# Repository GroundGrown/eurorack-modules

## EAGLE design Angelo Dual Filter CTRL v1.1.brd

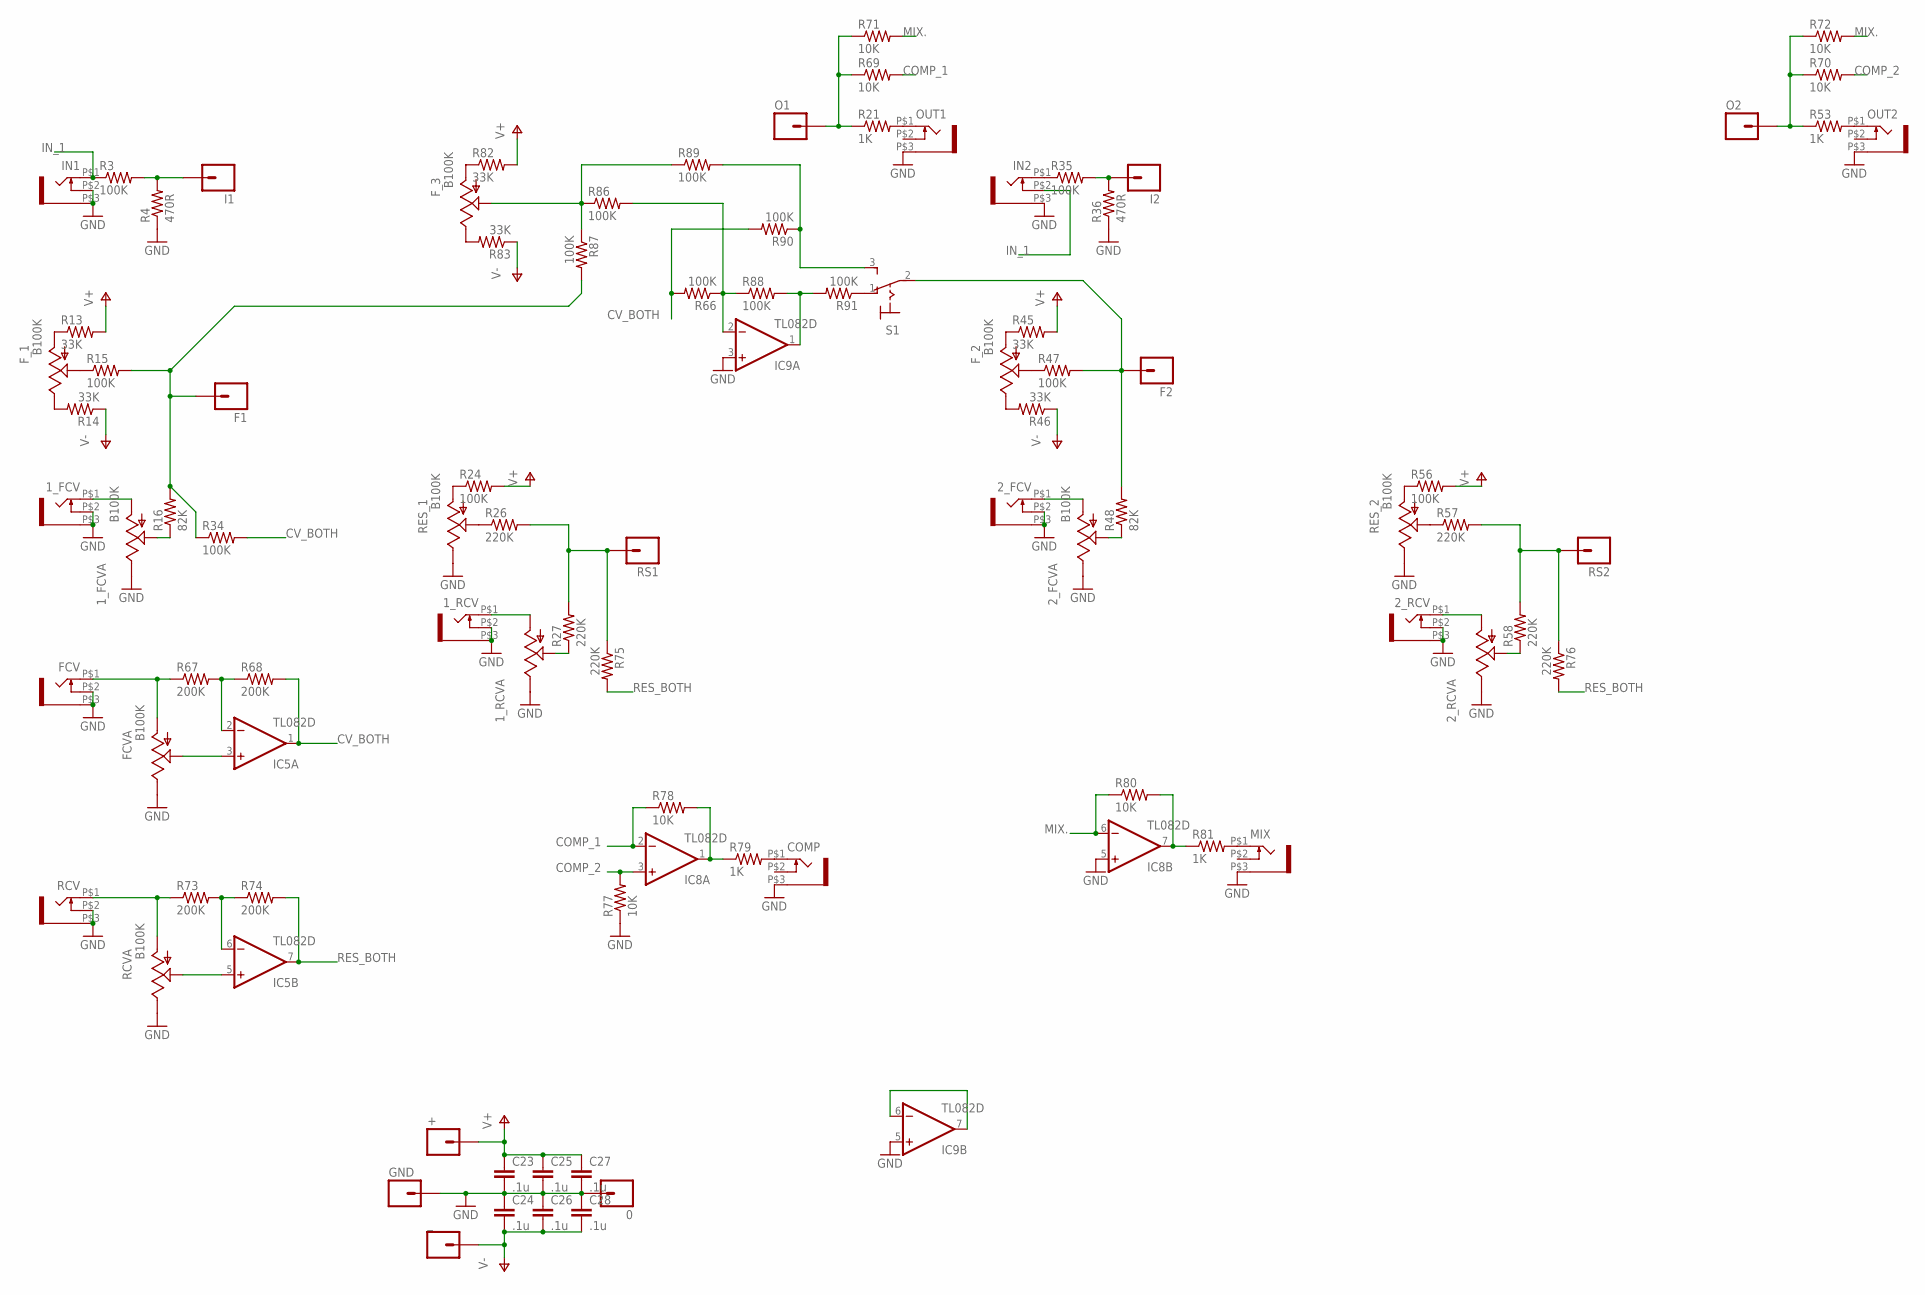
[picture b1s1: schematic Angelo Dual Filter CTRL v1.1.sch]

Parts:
0: M01PTH; 1X01
1_FCV, 1_RCV, 2_FCV, 2_RCV: WQP-PJ301M-12_JACK
1_FCVA, 2_FCVA: B100K; ALPS_POT
1_RCVA, 2_RCVA: POT; ALPS_POT
+: M01PTH; 1X01
C23, C24, C25, C26, C27, C28: .1u; 0805
COMP: WQP-PJ301M-12_JACK
F1, F2: M01PTH; 1X01
FCV: WQP-PJ301M-12_JACK
FCVA: B100K; ALPS_POT
F_1, F_2, F_3: B100K; ALPS_POT
GND: M01PTH; 1X01
I1, I2: M01PTH; 1X01
IC5, IC8, IC9: TL082D; SO08
IN1, IN2: WQP-PJ301M-12_JACK
MIX: WQP-PJ301M-12_JACK
O1, O2: M01PTH; 1X01
OUT1, OUT2: WQP-PJ301M-12_JACK
R3, R15, R24, R34, R35, R47, R56, R66, R86, R87, R88, R89, R90, R91: 100K; 0805
R4, R36: 470R; 0805
R13, R14, R45, R46, R82, R83: 33K; 0805
R16, R48: 82K; 0805
R21, R53, R79, R81: 1K; 0805
R26, R27, R57, R58, R75, R76: 220K; 0805
R67, R68, R73, R74: 200K; 0805
R69, R70, R71, R72, R77, R78, R80: 10K; 0805
RCV: WQP-PJ301M-12_JACK
RCVA: B100K; ALPS_POT
RES_1, RES_2: B100K; ALPS_POT
RS1, RS2: M01PTH; 1X01
S1: M9040P
_: M01PTH; 1X01

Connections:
COMP_1: IC8.2 (-IN), R69.2, R78.1
COMP_2: IC8.3 (+IN), R70.2, R77.2
CV_BOTH: IC5.1 (OUT), R34.2, R66.2, R68.2, R90.2
GND: 0.1, 1_FCV.P$2 (3), 1_FCV.P$3 (1), 1_FCVA.P$1 (E), 1_RCV.P$2 (3), 1_RCV.P$3 (1), 1_RCVA.P$1 (E), 2_FCV.P$2 (3), 2_FCV.P$3 (1), 2_FCVA.P$1 (E), 2_RCV.P$2 (3), 2_RCV.P$3 (1), 2_RCVA.P$1 (E), C23.2, C24.1, C25.2, C26.1, C27.2, C28.1, COMP.P$3 (1), FCV.P$2 (3), FCV.P$3 (1), FCVA.P$1 (E), GND.1, IC8.5 (+IN), IC9.3 (+IN), IC9.5 (+IN), IN1.P$2 (3), IN1.P$3 (1), IN2.P$3 (1), MIX.P$3 (1), OUT1.P$3 (1), OUT2.P$3 (1), R4.1, R36.1, R77.1, RCV.P$2 (3), RCV.P$3 (1), RCVA.P$1 (E), RES_1.P$1 (E), RES_2.P$1 (E)
IN_1: IN1.P$1 (2), IN2.P$2 (3), R3.1
MIX.: IC8.6 (-IN), R71.2, R72.2, R80.1
unnamed: F_3.P$3 (A), R82.1
unnamed: F_3.P$1 (E), R83.2
unnamed: I1.1, R3.2, R4.2
unnamed: COMP.P$1 (2), R79.2
unnamed: F_3.P$2 (S), R86.1, R87.1, R89.1
unnamed: F2.1, R47.2, R48.2, S1.2
unnamed: IC9.2 (-IN), R66.1, R86.2, R88.1
unnamed: IC9.6 (-IN), IC9.7 (OUT)
unnamed: IC9.1 (OUT), R88.2, R91.2
unnamed: R89.2, R90.1, S1.3 (S)
unnamed: R91.1, S1.1 (O)
unnamed: MIX.P$1 (2), R81.2
unnamed: F_1.P$3 (A), R13.1
unnamed: F_1.P$1 (E), R14.2
unnamed: 1_FCV.P$1 (2), 1_FCVA.P$3 (A)
unnamed: F_1.P$2 (S), R15.1
unnamed: 1_FCVA.P$2 (S), R16.1
unnamed: F1.1, R15.2, R16.2, R34.1, R87.2
unnamed: O1.1, R21.1, R69.1, R71.1
unnamed: OUT1.P$1 (2), R21.2
unnamed: R24.1, RES_1.P$3 (A)
unnamed: R26.2, R27.2, R75.1, RS1.1
unnamed: 1_RCV.P$1 (2), 1_RCVA.P$3 (A)
unnamed: R26.1, RES_1.P$2 (S)
unnamed: 1_RCVA.P$2 (S), R27.1
unnamed: I2.1, R35.2, R36.2
unnamed: IN2.P$1 (2), R35.1
unnamed: F_2.P$3 (A), R45.1
unnamed: F_2.P$1 (E), R46.2
unnamed: 2_FCV.P$1 (2), 2_FCVA.P$3 (A)
unnamed: F_2.P$2 (S), R47.1
unnamed: 2_FCVA.P$2 (S), R48.1
unnamed: O2.1, R53.1, R70.1, R72.1
unnamed: OUT2.P$1 (2), R53.2
unnamed: R56.1, RES_2.P$3 (A)
unnamed: 2_RCV.P$1 (2), 2_RCVA.P$3 (A)
unnamed: R57.1, RES_2.P$2 (S)
unnamed: 2_RCVA.P$2 (S), R58.1
unnamed: R57.2, R58.2, R76.1, RS2.1
unnamed: IC8.7 (OUT), R80.2, R81.1
unnamed: IC5.6 (-IN), R73.2, R74.1
unnamed: R73.1, RCV.P$1 (2), RCVA.P$3 (A)
unnamed: IC5.5 (+IN), RCVA.P$2 (S)
unnamed: IC8.1 (OUT), R78.2, R79.1
unnamed: IC5.2 (-IN), R67.2, R68.1
unnamed: FCV.P$1 (2), FCVA.P$3 (A), R67.1
unnamed: FCVA.P$2 (S), IC5.3 (+IN)
RES_BOTH: IC5.7 (OUT), R74.2, R75.2, R76.2
V+: +.1, C23.1, C25.1, C27.1, IC5.8 (V+), IC8.8 (V+), IC9.8 (V+), R13.2, R24.2, R45.2, R56.2, R82.2
V-: C24.2, C26.2, C28.2, IC5.4 (V-), IC8.4 (V-), IC9.4 (V-), R14.1, R46.1, R83.1, _.1

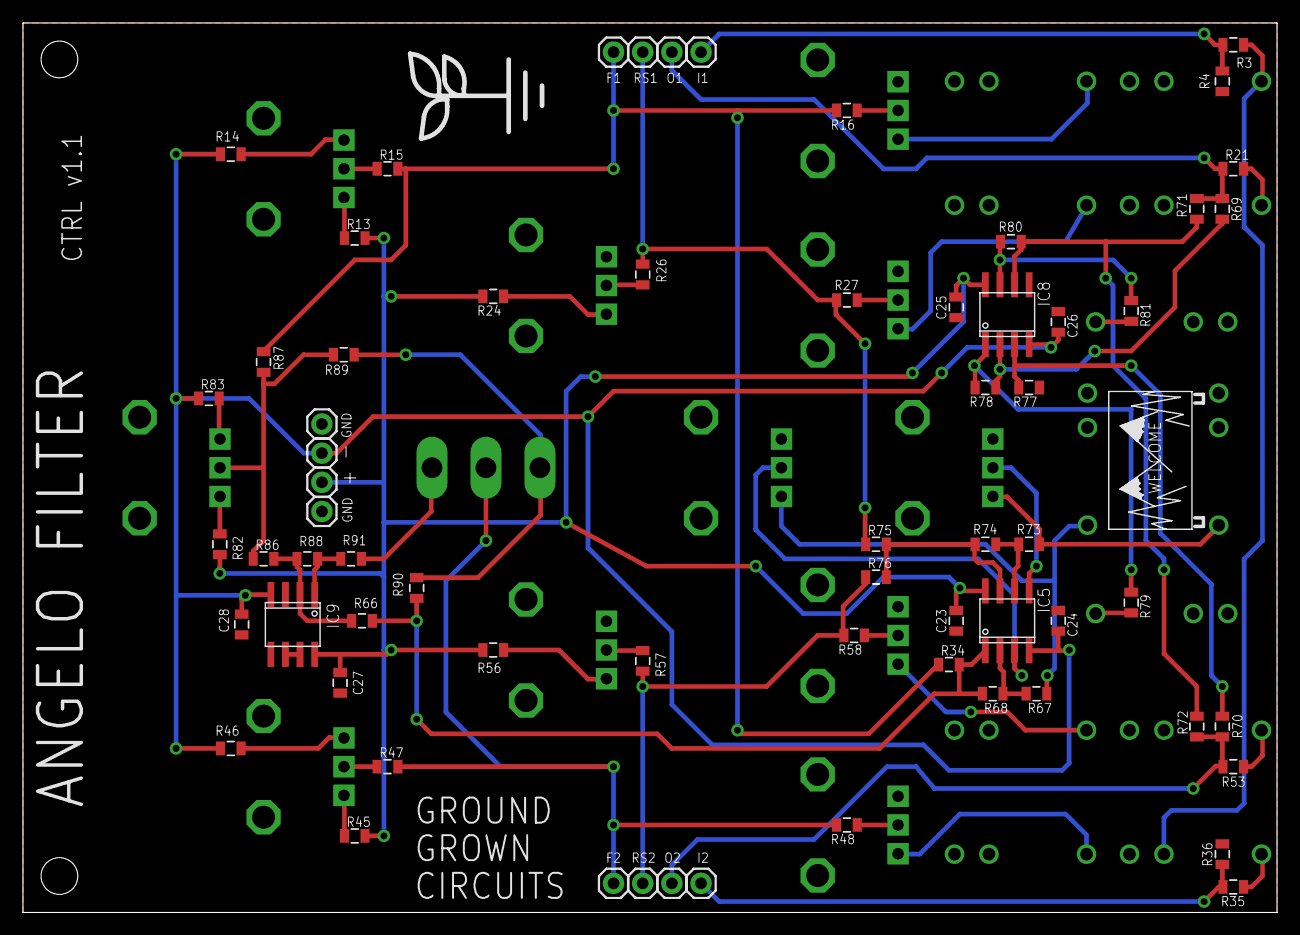
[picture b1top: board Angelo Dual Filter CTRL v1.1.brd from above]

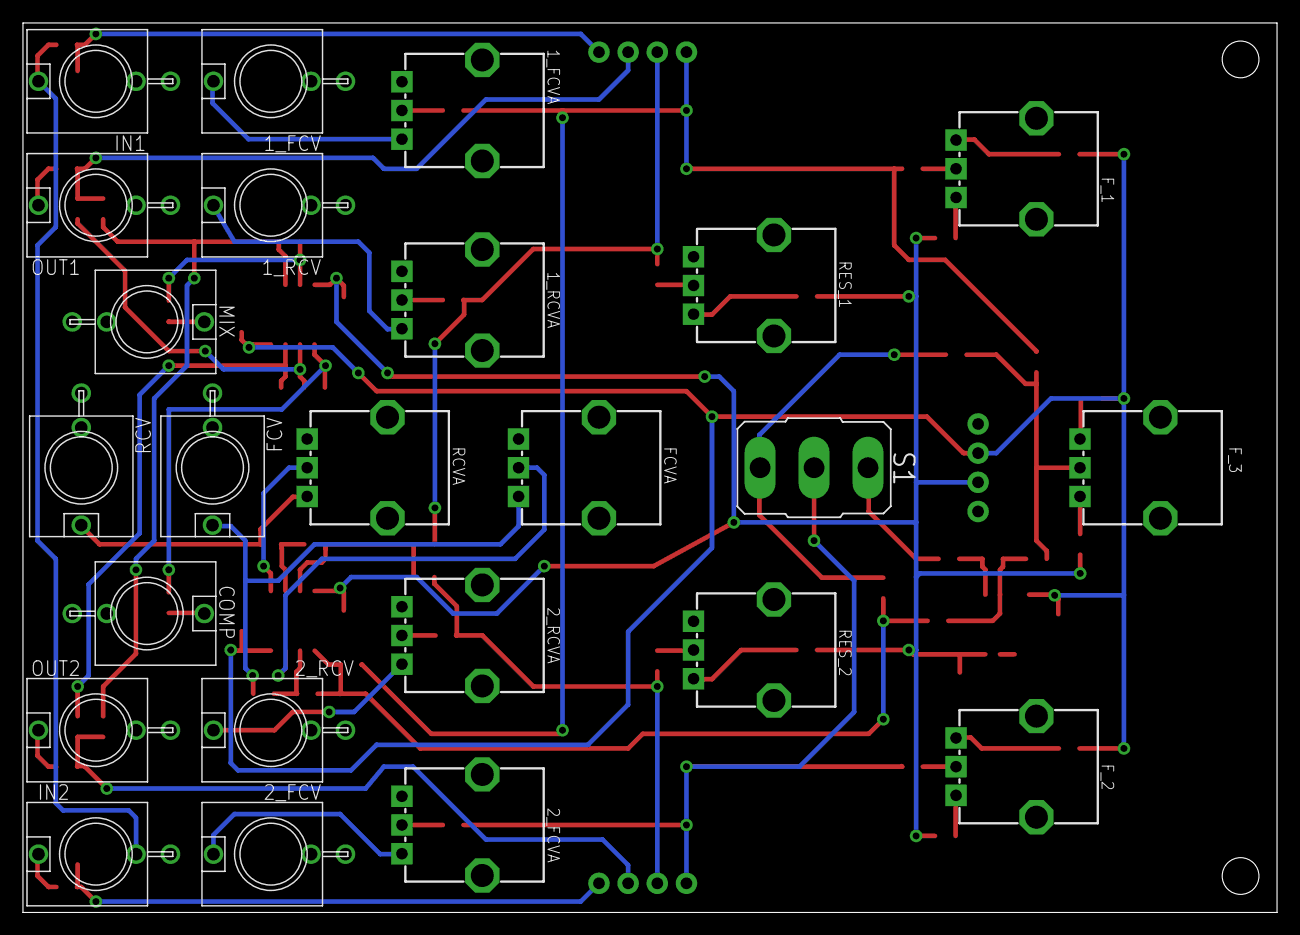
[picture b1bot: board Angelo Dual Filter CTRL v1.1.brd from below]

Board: 2 copper layers, 109.2 x 77.5 mm, 92 parts (24 on the bottom side), 56 nets.

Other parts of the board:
U$1: LOGO_MED
U$2: WELCOME_SIGN

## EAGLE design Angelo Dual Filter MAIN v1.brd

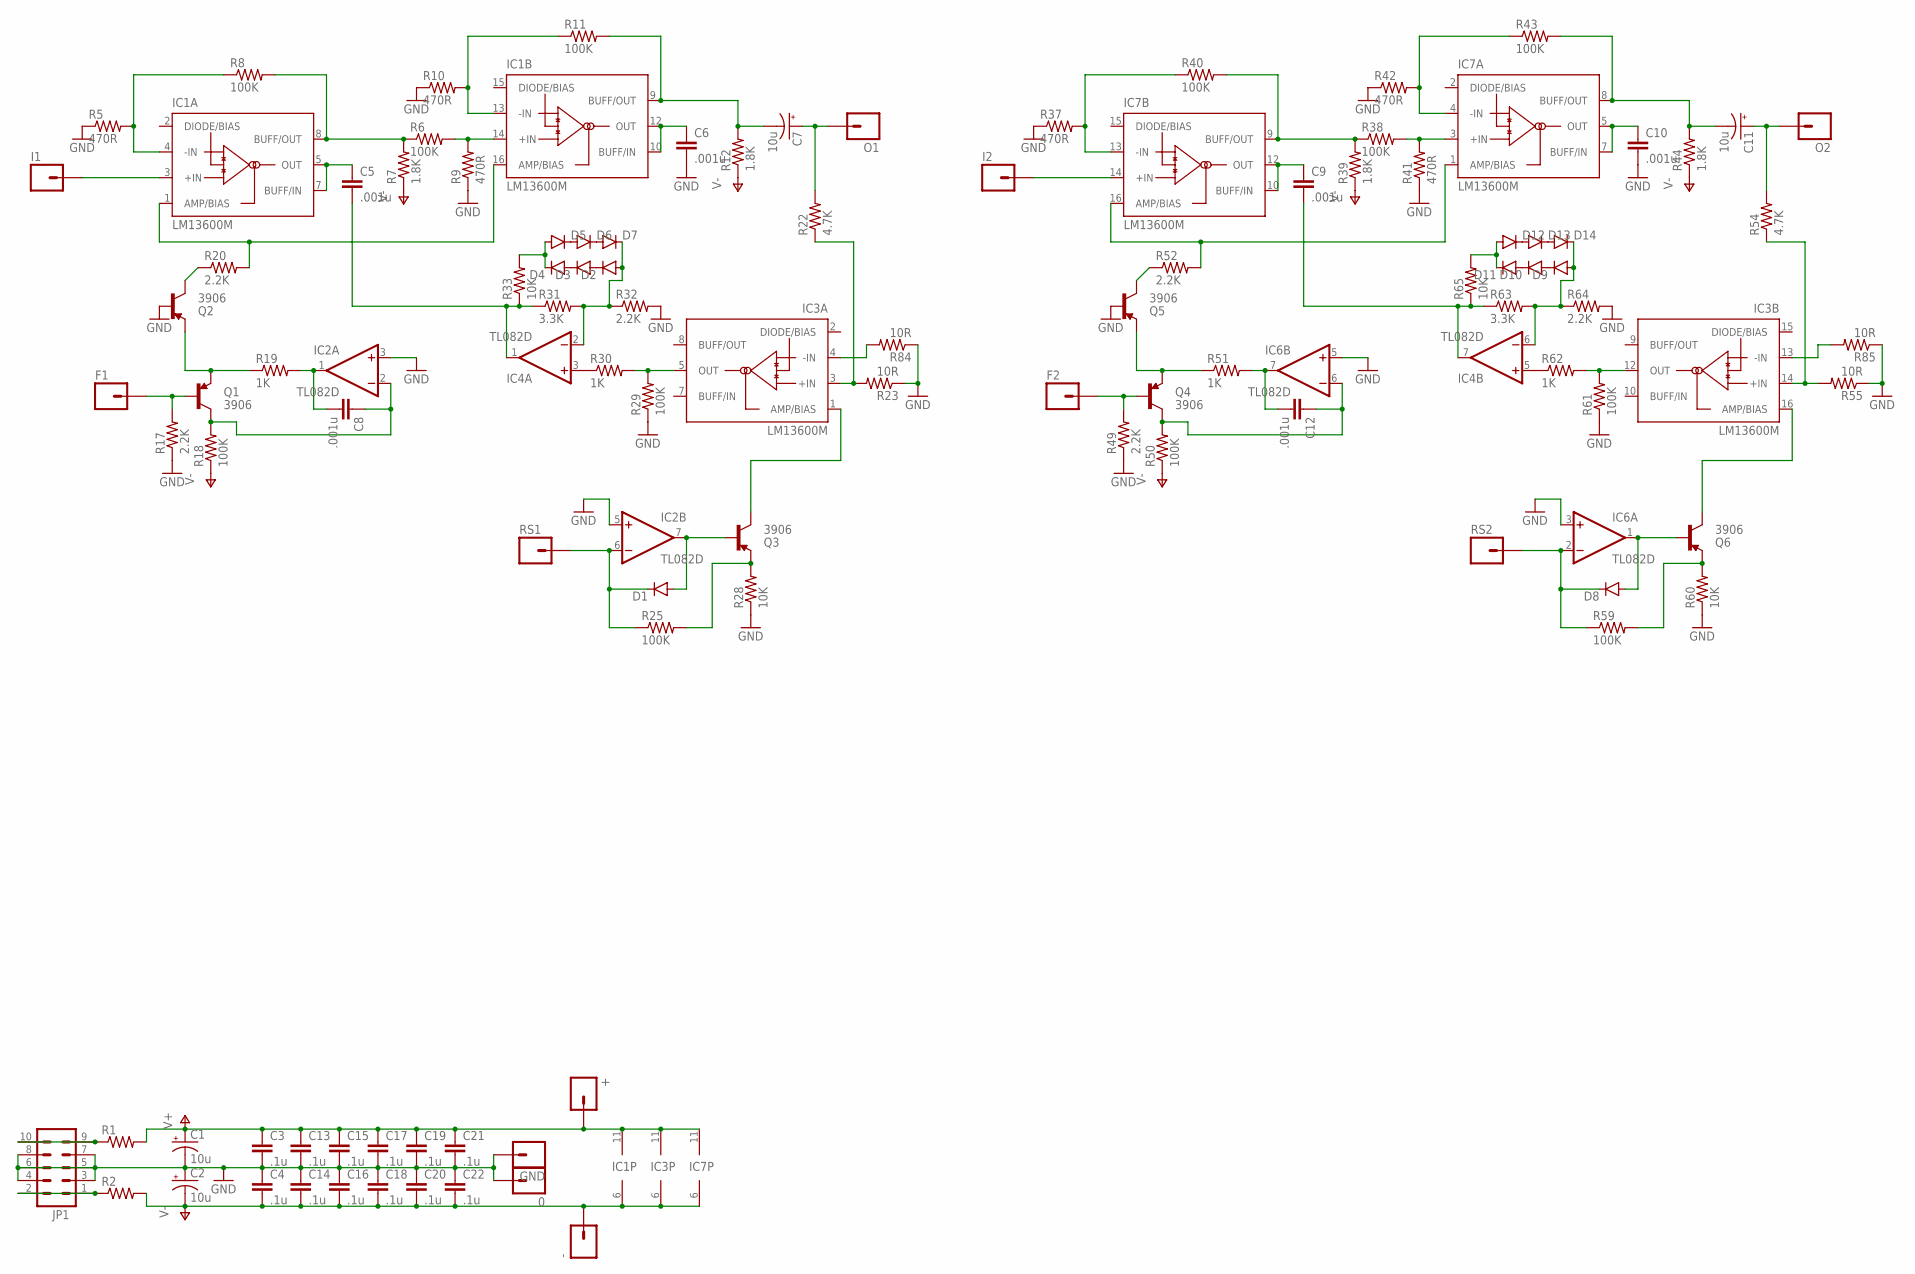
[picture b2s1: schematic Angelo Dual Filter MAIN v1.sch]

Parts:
0: M01PTH; 1X01
+: M01PTH; 1X01
-: M01PTH; 1X01
C1, C2, C7, C11: 10u; CPOL-RADIAL-10UF-25V
C3, C4, C13, C14, C15, C16, C17, C18, C19, C20, C21, C22: .1u; 0805
C5, C6, C9, C10: .001u; C5B2.5
C8, C12: .001u; 0805
D1, D2, D3, D4, D5, D6, D7, D8, D9, D10, D11, D12, D13, D14: DIODESOD123; SOD-123
F1, F2: M01PTH; 1X01
GND: M01PTH; 1X01
I1, I2: M01PTH; 1X01
IC1, IC3, IC7: LM13600M; SO16
IC2, IC4, IC6: TL082D; SO08
JP1: M05X2PTH; AVR_ICSP
O1, O2: M01PTH; 1X01
Q1, Q2, Q3, Q4, Q5, Q6: 3906; SOT23-3
R1, R2: RESISTOR0805-RES; 0805
R5, R9, R10, R37, R41, R42: 470R; 0805
R6, R8, R11, R18, R25, R29, R38, R40, R43, R50, R59, R61: 100K; 0805
R7, R12, R39, R44: 1.8K; 0805
R17, R20, R32, R49, R52, R64: 2.2K; 0805
R19, R30, R51, R62: 1K; 0805
R22, R54: 4.7K; 0805
R23, R55, R84, R85: 10R; 0805
R28, R33, R60, R65: 10K; 0805
R31, R63: 3.3K; 0805
RS1, RS2: M01PTH; 1X01

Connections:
GND: 0.1, C1.2 (-), C2.1 (+), C3.2, C4.1, C6.2, C10.2, C13.2, C14.1, C15.2, C16.1, C17.2, C18.1, C19.2, C20.1, C21.2, C22.1, GND.1, IC2.3 (+IN), IC2.5 (+IN), IC6.3 (+IN), IC6.5 (+IN), JP1.3, JP1.4, JP1.5, JP1.6, JP1.7, JP1.8, Q2.1 (B), Q5.1 (B), R5.1, R9.1, R10.1, R17.1, R23.1, R28.1, R29.1, R32.2, R37.1, R41.1, R42.1, R49.1, R55.1, R60.1, R61.1, R64.2, R84.1, R85.1
unnamed: JP1.9, JP1.10, R1.1
unnamed: JP1.1, JP1.2, R2.1
unnamed: I1.1, IC1.3 (+IN)
unnamed: I2.1, IC7.14 (+IN)
unnamed: IC1.4 (-IN), R5.2, R8.1
unnamed: C5.1, IC1.5 (OUT), IC1.7 (BUFF/IN)
unnamed: C6.1, IC1.10 (BUFF/IN), IC1.12 (OUT)
unnamed: IC1.8 (BUFF/OUT), R6.1, R7.2, R8.2
unnamed: IC1.14 (+IN), R6.2, R9.2
unnamed: IC1.13 (-IN), R10.2, R11.1
unnamed: C7.2 (-), IC1.9 (BUFF/OUT), R11.2, R12.2
unnamed: C8.1, IC2.2 (-IN), Q1.3 (C), R18.2
unnamed: C8.2, IC2.1 (OUT), R19.2
unnamed: Q1.2 (E), Q2.2 (E), R19.1
unnamed: Q2.3 (C), R20.1
unnamed: IC1.1 (AMP/BIAS), IC1.16 (AMP/BIAS), R20.2
unnamed: IC3.3 (+IN), R22.1, R23.2
unnamed: C7.1 (+), O1.1, R22.2
unnamed: D1.C, IC2.6 (-IN), R25.1, RS1.1
unnamed: D1.A, IC2.7 (OUT), Q3.1 (B)
unnamed: Q3.2 (E), R25.2, R28.2
unnamed: IC3.1 (AMP/BIAS), Q3.3 (C)
unnamed: IC3.5 (OUT), R29.2, R30.2
unnamed: IC4.3 (+IN), R30.1
unnamed: D2.A, D7.C, IC4.2 (-IN), R31.2, R32.1
unnamed: D2.C, D3.A
unnamed: D3.C, D4.A
unnamed: D5.C, D6.A
unnamed: D6.C, D7.A
unnamed: D4.C, D5.A, R33.2
unnamed: C5.2, IC4.1 (OUT), R31.1, R33.1
unnamed: IC7.13 (-IN), R37.2, R40.1
unnamed: C9.1, IC7.10 (BUFF/IN), IC7.12 (OUT)
unnamed: IC7.9 (BUFF/OUT), R38.1, R39.2, R40.2
unnamed: IC7.3 (+IN), R38.2, R41.2
unnamed: IC7.4 (-IN), R42.2, R43.1
unnamed: C11.2 (-), IC7.8 (BUFF/OUT), R43.2, R44.2
unnamed: C10.1, IC7.5 (OUT), IC7.7 (BUFF/IN)
unnamed: C12.1, IC6.6 (-IN), Q4.3 (C), R50.2
unnamed: C12.2, IC6.7 (OUT), R51.2
unnamed: Q4.2 (E), Q5.2 (E), R51.1
unnamed: IC7.1 (AMP/BIAS), IC7.16 (AMP/BIAS), R52.2
unnamed: F2.1, Q4.1 (B), R49.2
unnamed: C11.1 (+), O2.1, R54.2
unnamed: IC3.14 (+IN), R54.1, R55.2
unnamed: D8.C, IC6.2 (-IN), R59.1, RS2.1
unnamed: Q5.3 (C), R52.1
unnamed: D8.A, IC6.1 (OUT), Q6.1 (B)
unnamed: Q6.2 (E), R59.2, R60.2
unnamed: IC3.16 (AMP/BIAS), Q6.3 (C)
unnamed: IC3.12 (OUT), R61.2, R62.2
unnamed: IC4.5 (+IN), R62.1
unnamed: D9.A, D14.C, IC4.6 (-IN), R63.2, R64.1
unnamed: D9.C, D10.A
unnamed: D10.C, D11.A
unnamed: D12.C, D13.A
unnamed: D13.C, D14.A
unnamed: D11.C, D12.A, R65.2
unnamed: C9.2, IC4.7 (OUT), R63.1, R65.1
unnamed: IC3.4 (-IN), R84.2
unnamed: IC3.13 (-IN), R85.2
unnamed: F1.1, Q1.1 (B), R17.2
V+: +.1, C1.1 (+), C3.1, C13.1, C15.1, C17.1, C19.1, C21.1, IC1.11 (V+), IC2.8 (V+), IC3.11 (V+), IC4.8 (V+), IC6.8 (V+), IC7.11 (V+), R1.2
V-: -.1, C2.2 (-), C4.2, C14.2, C16.2, C18.2, C20.2, C22.2, IC1.6 (V-), IC2.4 (V-), IC3.6 (V-), IC4.4 (V-), IC6.4 (V-), IC7.6 (V-), R2.2, R7.1, R12.1, R18.1, R39.1, R44.1, R50.1

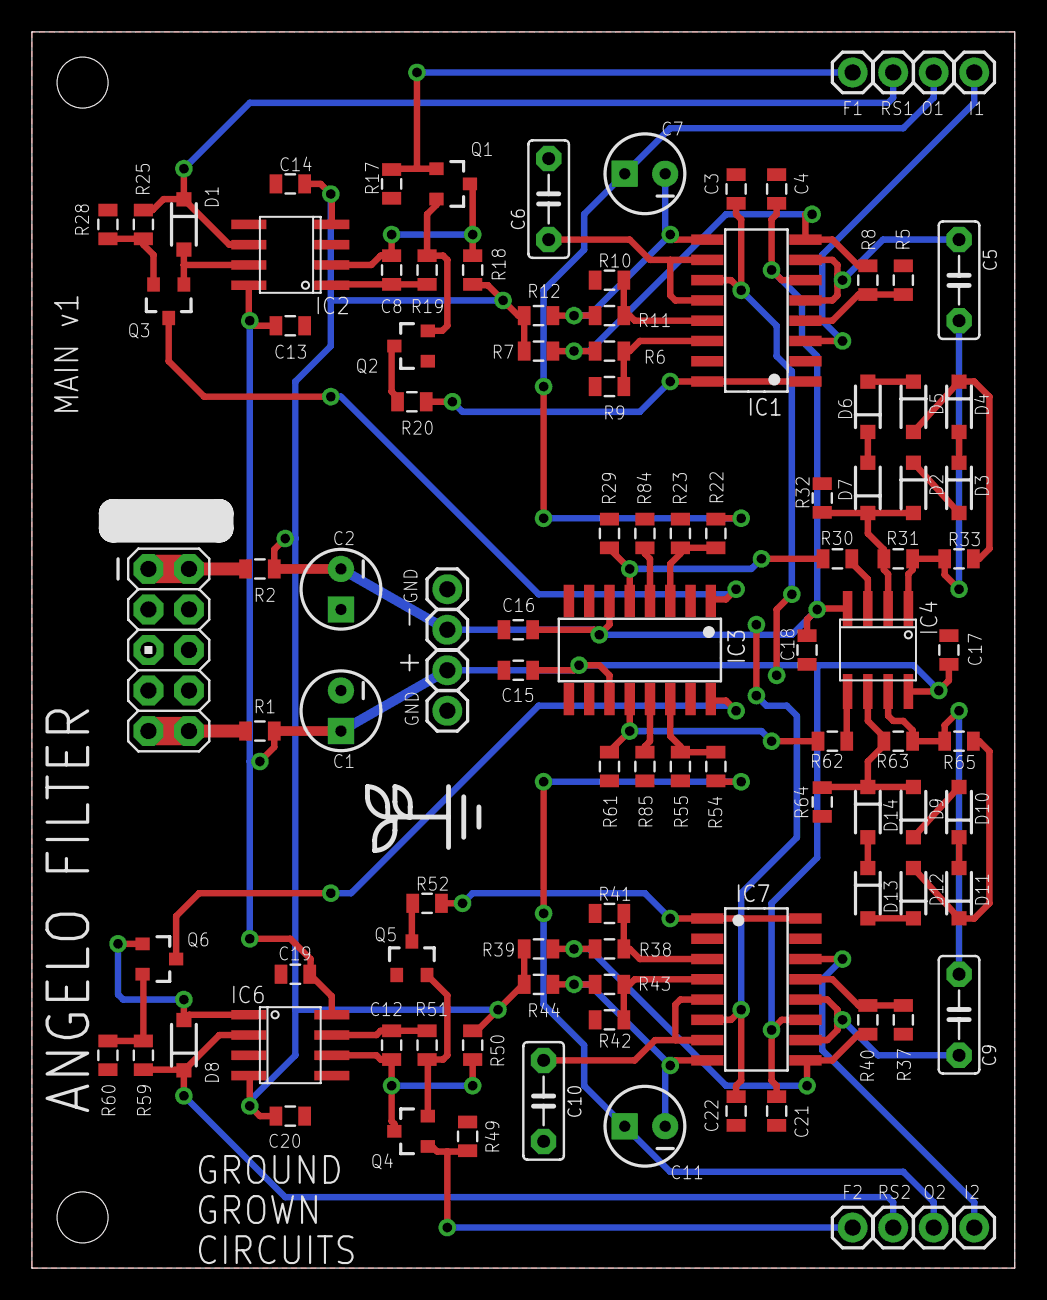
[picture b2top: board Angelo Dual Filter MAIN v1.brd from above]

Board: 2 copper layers, 61.6 x 77.5 mm, 108 parts (0 on the bottom side), 65 nets.

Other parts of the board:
U$1: LOGO_SMALL

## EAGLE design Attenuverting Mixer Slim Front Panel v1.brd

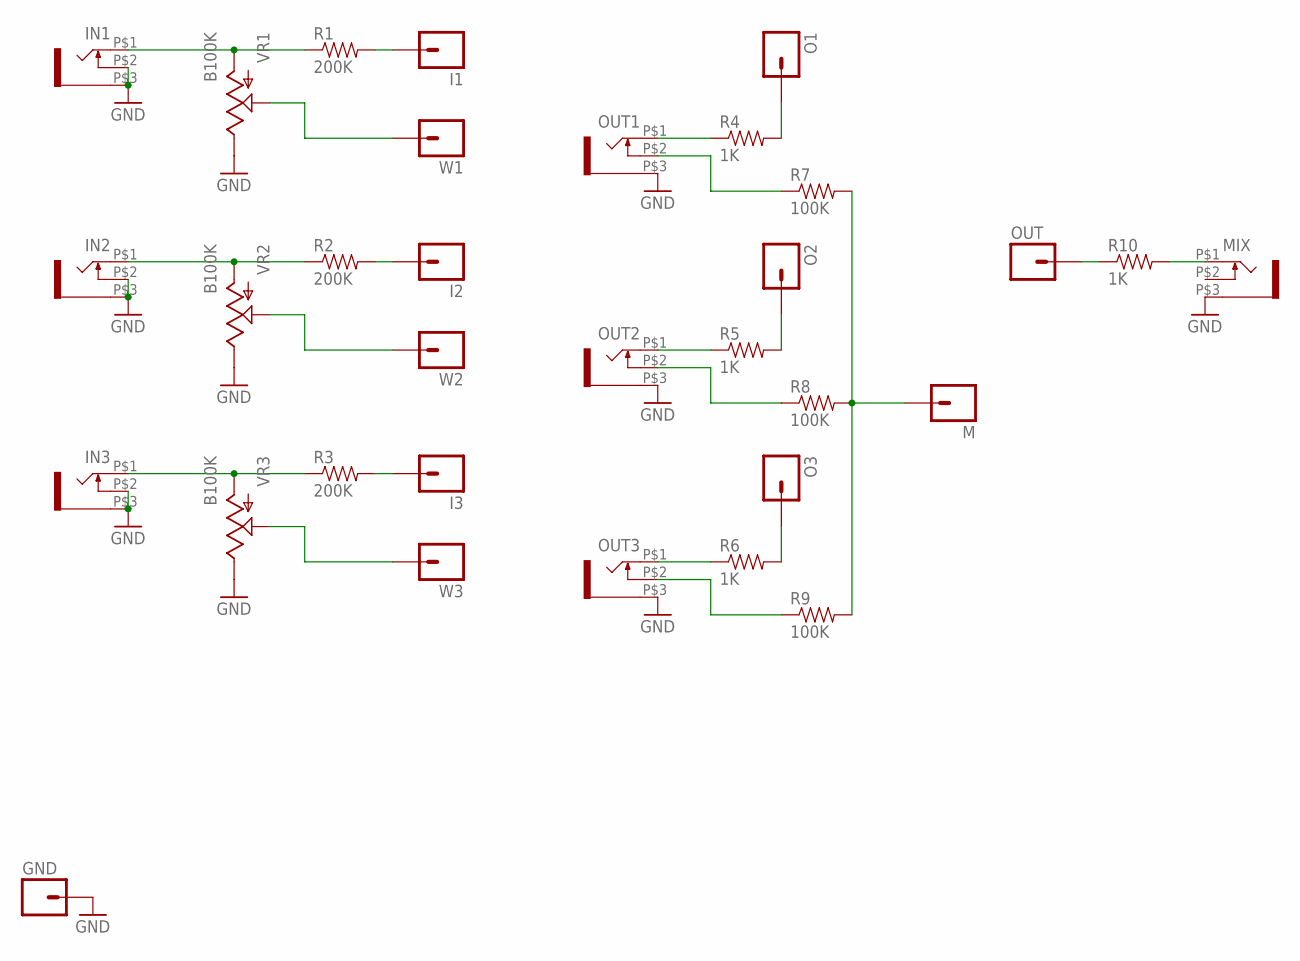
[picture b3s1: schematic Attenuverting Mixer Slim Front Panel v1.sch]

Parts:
GND: M01PTH; 1X01
I1, I2, I3: M01PTH; 1X01
IN1, IN2, IN3: WQP-PJ301M-12_JACK
M: M01PTH; 1X01
MIX: WQP-PJ301M-12_JACK
O1, O2, O3: M01PTH; 1X01
OUT: M01PTH; 1X01
OUT1, OUT2, OUT3: WQP-PJ301M-12_JACK
R1, R2, R3: 200K; 0805
R4, R5, R6, R10: 1K; 0805
R7, R8, R9: 100K; 0805
VR1, VR2, VR3: B100K; ALPS_POT
W1, W2, W3: M01PTH; 1X01

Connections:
GND: GND.1, IN1.P$2 (3), IN1.P$3 (1), IN2.P$2 (3), IN2.P$3 (1), IN3.P$2 (3), IN3.P$3 (1), MIX.P$3 (1), OUT1.P$3 (1), OUT2.P$3 (1), OUT3.P$3 (1), VR1.P$1 (E), VR2.P$1 (E), VR3.P$1 (E)
unnamed: IN1.P$1 (2), R1.1, VR1.P$3 (A)
unnamed: I1.1, R1.2
unnamed: VR1.P$2 (S), W1.1
unnamed: IN2.P$1 (2), R2.1, VR2.P$3 (A)
unnamed: I2.1, R2.2
unnamed: VR2.P$2 (S), W2.1
unnamed: IN3.P$1 (2), R3.1, VR3.P$3 (A)
unnamed: I3.1, R3.2
unnamed: VR3.P$2 (S), W3.1
unnamed: OUT1.P$1 (2), R4.1
unnamed: OUT2.P$1 (2), R5.1
unnamed: O2.1, R5.2
unnamed: O1.1, R4.2
unnamed: OUT3.P$1 (2), R6.1
unnamed: O3.1, R6.2
unnamed: OUT3.P$2 (3), R9.1
unnamed: OUT2.P$2 (3), R8.1
unnamed: OUT1.P$2 (3), R7.1
unnamed: M.1, R7.2, R8.2, R9.2
unnamed: OUT.1, R10.1
unnamed: MIX.P$1 (2), R10.2

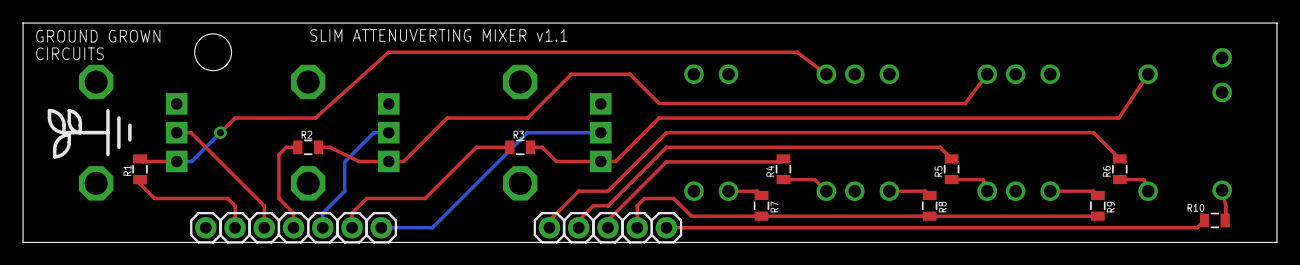
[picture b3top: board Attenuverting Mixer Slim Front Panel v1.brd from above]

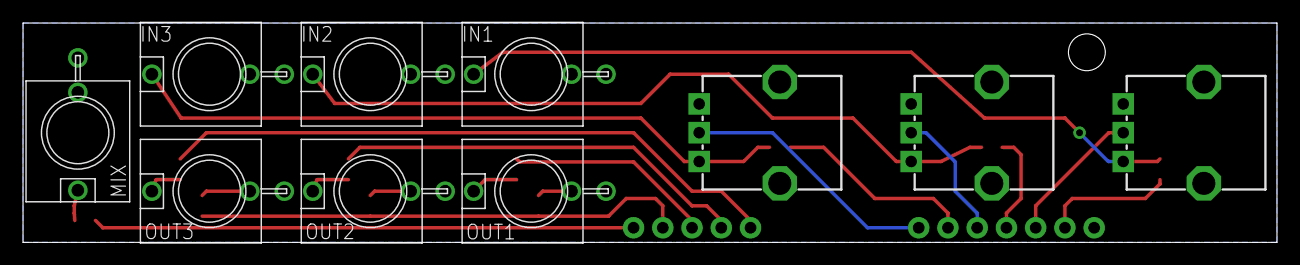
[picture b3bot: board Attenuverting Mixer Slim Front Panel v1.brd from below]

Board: 2 copper layers, 108.9 x 19.1 mm, 33 parts (10 on the bottom side), 22 nets.

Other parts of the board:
U$1: LOGO_SMALL

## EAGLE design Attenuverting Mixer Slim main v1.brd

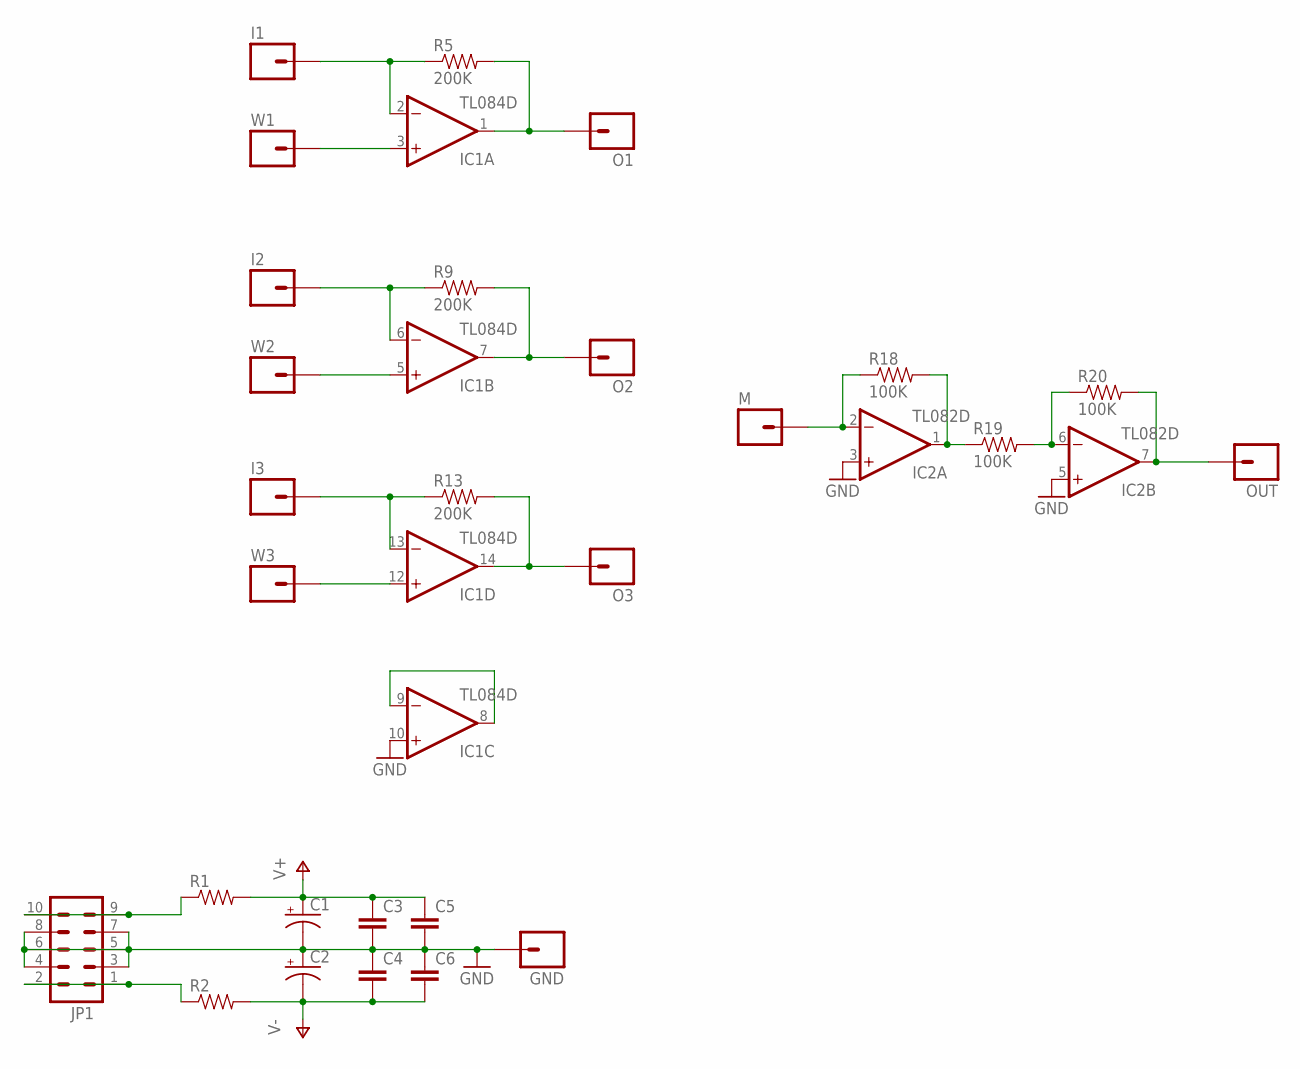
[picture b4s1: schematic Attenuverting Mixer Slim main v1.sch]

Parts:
C1, C2: CAP_POLC; PANASONIC_C
C3, C4, C5, C6: CAP0603-CAP; 0603-CAP
GND: M01PTH; 1X01
I1, I2, I3: M01PTH; 1X01
IC1: TL084D; SO14
IC2: TL082D; SO08
JP1: M05X2PTH; AVR_ICSP
M: M01PTH; 1X01
O1, O2, O3: M01PTH; 1X01
OUT: M01PTH; 1X01
R1, R2: RESISTOR0805-RES; 0805
R5, R9, R13: 200K; 0603-RES
R18, R19, R20: 100K; 0603-RES
W1, W2, W3: M01PTH; 1X01

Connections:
GND: C1.-, C2.+, C3.2, C4.1, C5.2, C6.1, GND.1, IC1.10 (+IN), IC2.3 (+IN), IC2.5 (+IN), JP1.3, JP1.4, JP1.5, JP1.6, JP1.7, JP1.8
unnamed: IC1.3 (+IN), W1.1
unnamed: I1.1, IC1.2 (-IN), R5.1
unnamed: JP1.1, JP1.2, R2.1
unnamed: JP1.9, JP1.10, R1.1
unnamed: IC1.1 (OUT), O1.1, R5.2
unnamed: IC1.5 (+IN), W2.1
unnamed: IC1.12 (+IN), W3.1
unnamed: I2.1, IC1.6 (-IN), R9.1
unnamed: IC1.7 (OUT), O2.1, R9.2
unnamed: I3.1, IC1.13 (-IN), R13.1
unnamed: IC1.14 (OUT), O3.1, R13.2
unnamed: IC2.2 (-IN), M.1, R18.1
unnamed: IC2.1 (OUT), R18.2, R19.1
unnamed: IC2.6 (-IN), R19.2, R20.1
unnamed: IC2.7 (OUT), OUT.1, R20.2
unnamed: IC1.8 (OUT), IC1.9 (-IN)
V+: C1.+, C3.1, C5.1, IC1.4 (V+), IC2.8 (V+), R1.2
V-: C2.-, C4.2, C6.2, IC1.11 (V-), IC2.4 (V-), R2.2

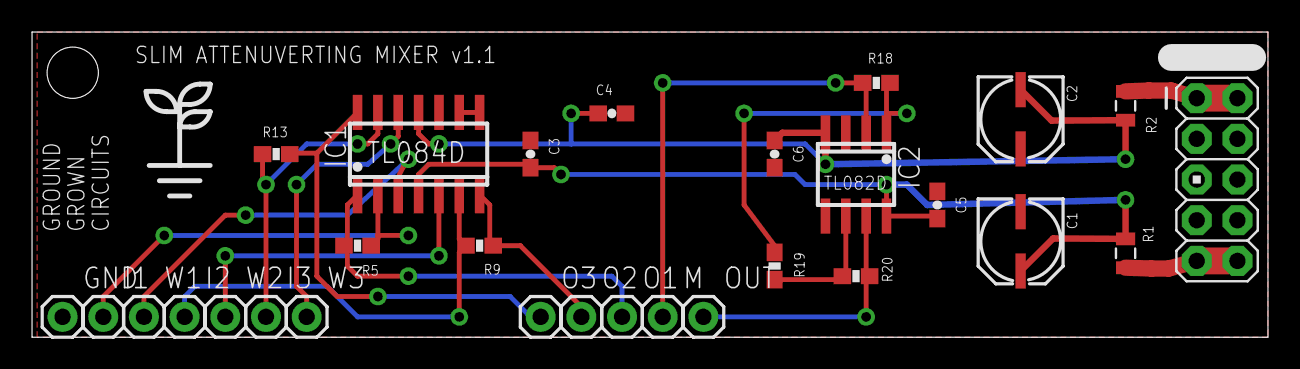
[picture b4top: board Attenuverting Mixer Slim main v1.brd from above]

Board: 2 copper layers, 77.2 x 19.0 mm, 30 parts (0 on the bottom side), 19 nets.

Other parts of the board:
U$1: LOGO_SMALL

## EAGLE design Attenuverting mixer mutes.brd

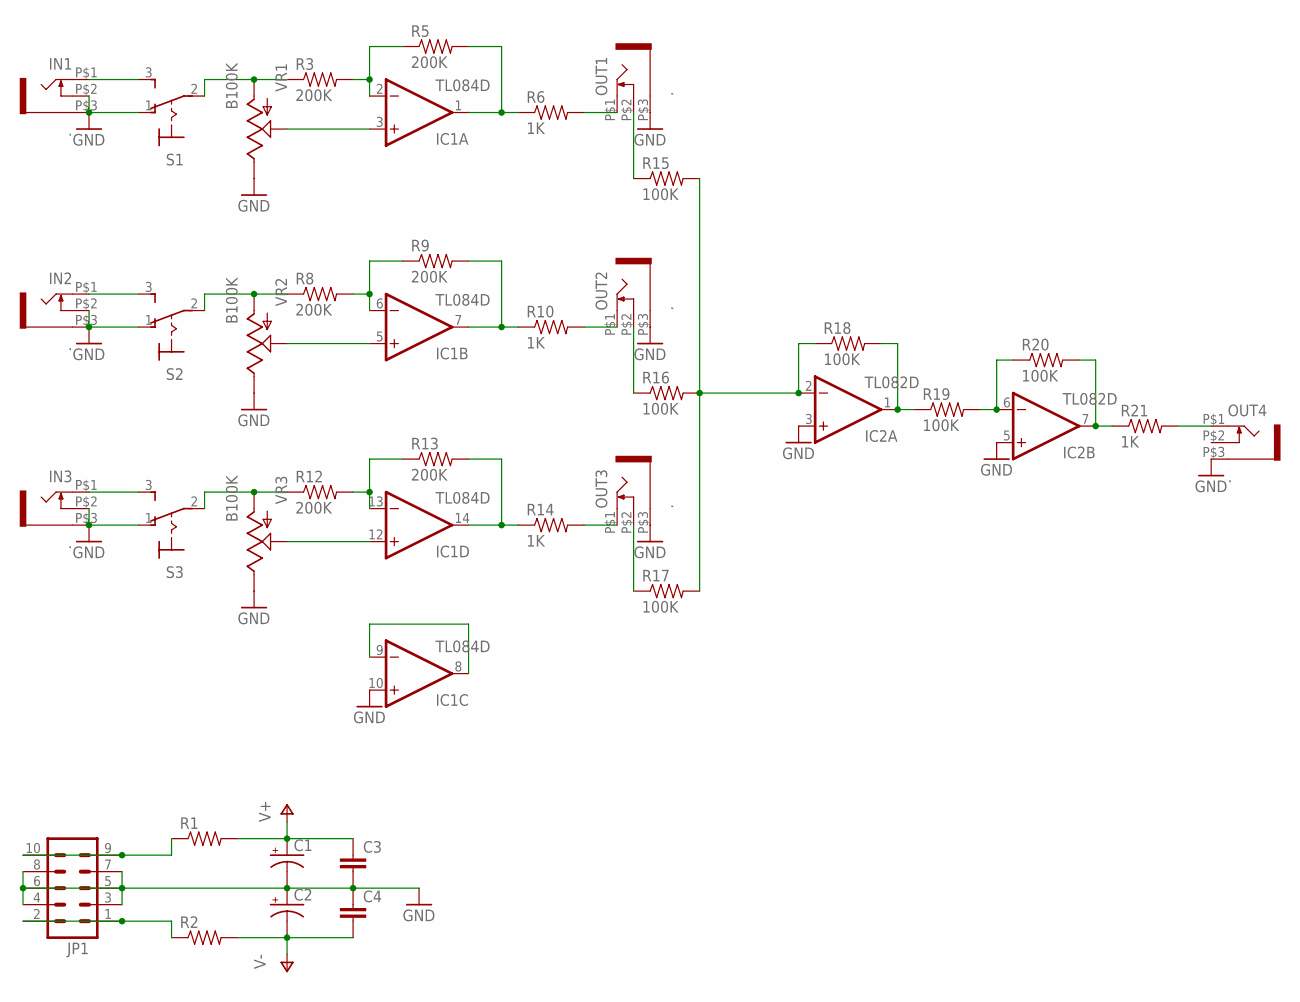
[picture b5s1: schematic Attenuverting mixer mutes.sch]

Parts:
C1, C2: CAP_POLD; PANASONIC_D
C3, C4: CAP0603-CAP; 0603-CAP
IC1: TL084D; SO14
IC2: TL082D; SO08
IN1, IN2, IN3: .; WQP-PJ301M-12_JACK
JP1: M05X2PTH; AVR_ICSP
OUT1, OUT2, OUT3, OUT4: .; WQP-PJ301M-12_JACK
R1, R2: RESISTOR0805-RES; 0805
R3, R5, R8, R9, R12, R13: 200K; 0603-RES
R6, R10, R14, R21: 1K; 0603-RES
R15, R16, R17, R18, R19, R20: 100K; 0603-RES
S1, S2, S3: M9040P
VR1, VR2, VR3: B100K; ALPS_POT

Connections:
GND: C1.-, C2.+, C3.2, C4.1, IC1.10 (+IN), IC2.3 (+IN), IC2.5 (+IN), IN1.P$2 (3), IN1.P$3 (1), IN2.P$2 (3), IN2.P$3 (1), IN3.P$2 (3), IN3.P$3 (1), JP1.3, JP1.4, JP1.5, JP1.6, JP1.7, JP1.8, OUT1.P$3 (1), OUT2.P$3 (1), OUT3.P$3 (1), OUT4.P$3 (1), S1.1 (O), S2.1 (O), S3.1 (O), VR1.P$1 (E), VR2.P$1 (E), VR3.P$1 (E)
unnamed: R3.1, S1.2, VR1.P$3 (A)
unnamed: IC1.2 (-IN), R3.2, R5.1
unnamed: JP1.1, JP1.2, R2.1
unnamed: JP1.9, JP1.10, R1.1
unnamed: OUT3.P$1 (2), R14.2
unnamed: OUT2.P$1 (2), R10.2
unnamed: OUT1.P$1 (2), R6.2
unnamed: IC1.1 (OUT), R5.2, R6.1
unnamed: IC1.3 (+IN), VR1.P$2 (S)
unnamed: R8.1, S2.2, VR2.P$3 (A)
unnamed: IC1.6 (-IN), R8.2, R9.1
unnamed: IC1.5 (+IN), VR2.P$2 (S)
unnamed: IC1.7 (OUT), R9.2, R10.1
unnamed: R12.1, S3.2, VR3.P$3 (A)
unnamed: IC1.12 (+IN), VR3.P$2 (S)
unnamed: IC1.13 (-IN), R12.2, R13.1
unnamed: IC1.14 (OUT), R13.2, R14.1
unnamed: OUT1.P$2 (3), R15.1
unnamed: OUT2.P$2 (3), R16.1
unnamed: OUT3.P$2 (3), R17.1
unnamed: IC2.2 (-IN), R15.2, R16.2, R17.2, R18.1
unnamed: IC2.1 (OUT), R18.2, R19.1
unnamed: IC2.6 (-IN), R19.2, R20.1
unnamed: IC2.7 (OUT), R20.2, R21.1
unnamed: OUT4.P$1 (2), R21.2
unnamed: IC1.8 (OUT), IC1.9 (-IN)
unnamed: IN3.P$1 (2), S3.3 (S)
unnamed: IN2.P$1 (2), S2.3 (S)
unnamed: IN1.P$1 (2), S1.3 (S)
V+: C1.+, C3.1, IC1.4 (V+), IC2.8 (V+), R1.2
V-: C2.-, C4.2, IC1.11 (V-), IC2.4 (V-), R2.2

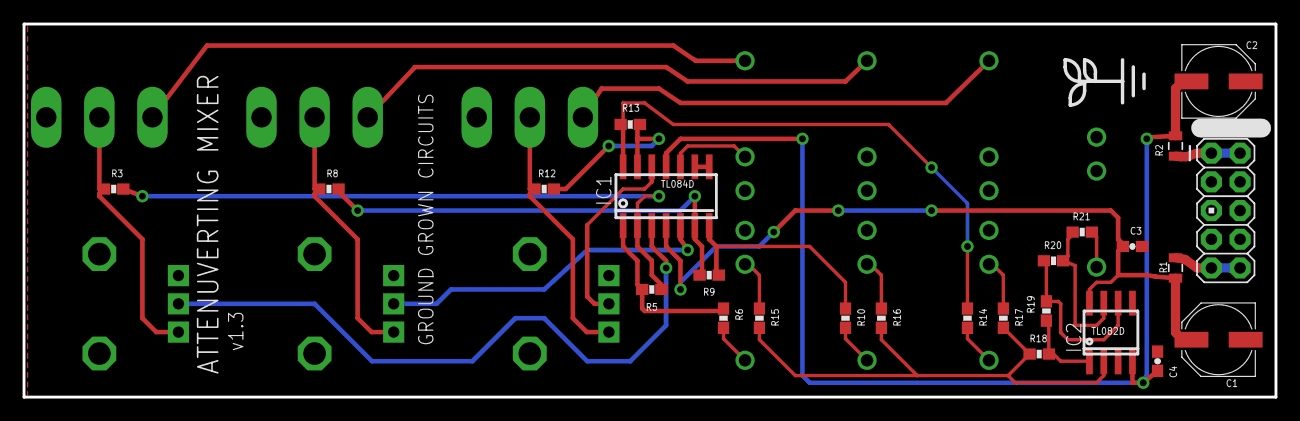
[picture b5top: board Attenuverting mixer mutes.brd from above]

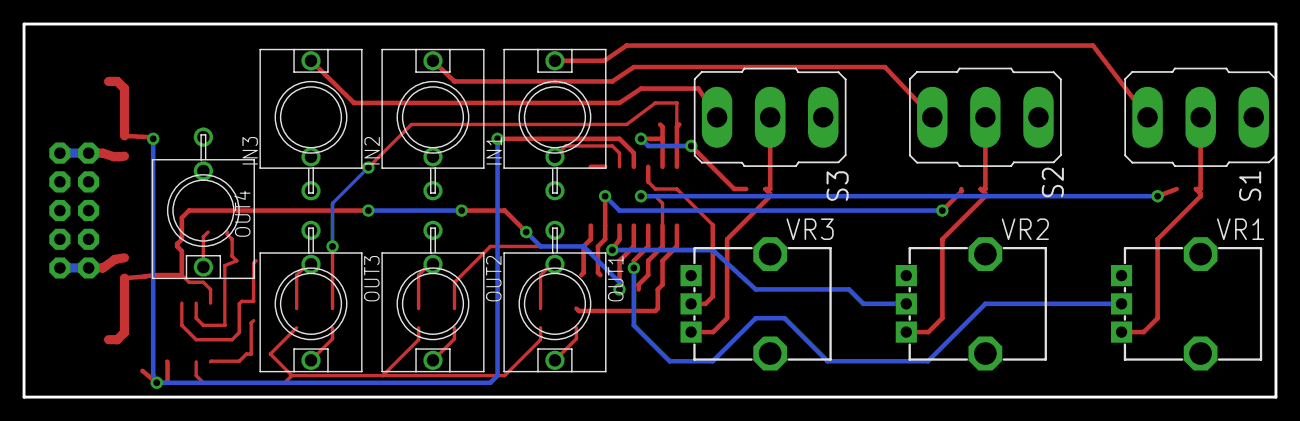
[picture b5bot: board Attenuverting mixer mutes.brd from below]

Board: 2 copper layers, 110.8 x 33.0 mm, 39 parts (13 on the bottom side), 32 nets.

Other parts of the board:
U$1: LOGO_SMALL

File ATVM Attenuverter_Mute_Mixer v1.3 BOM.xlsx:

2 | FERRITE BEAD | R1, R2
4 | 1K | R6, R10, R14, R21
6 | 100K | R15, R16, R17, R18, R19, R20
6 | 200K | R3, R5, R8, R9, R12, R13
2 | .1u | C3, C4
2 | 10u | C1, C2
1 | TL084 | IC1
1 | TL082 | IC2
1 | 2x5 pos male .1" Header | JP1
3 | B100K | VR1, VR2, VR3
7 | WQP-PJ301M-12_JACK | IN1, IN2, IN3, OUT1, OUT2, OUT3, MIX
3 | ON-ON toggle M9040P | S1, S2, S3

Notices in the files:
parts and their libraries:
SparkFun-Connectors: Licensing: Creative Commons ShareAlike 4.0 International - https://creativecommons.org/licenses/by-sa/4.0
